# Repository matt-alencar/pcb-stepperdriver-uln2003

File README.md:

# Basic PCB based on ULN2003

Basic dual layer PCB project based on ULN2003 darlington transistor array, commonly used to drive unipolar stepper motor such as 28BYJ-48.

## Prerequisites

	Last version of KiCad software

## Versioning

	29/01/2019 - Initial work (V1.1)

## Authors

* **Matheus Alencar Nascimento** - *Initial work*

## License

This project is licensed under the MIT License - see the [LICENSE] file for details

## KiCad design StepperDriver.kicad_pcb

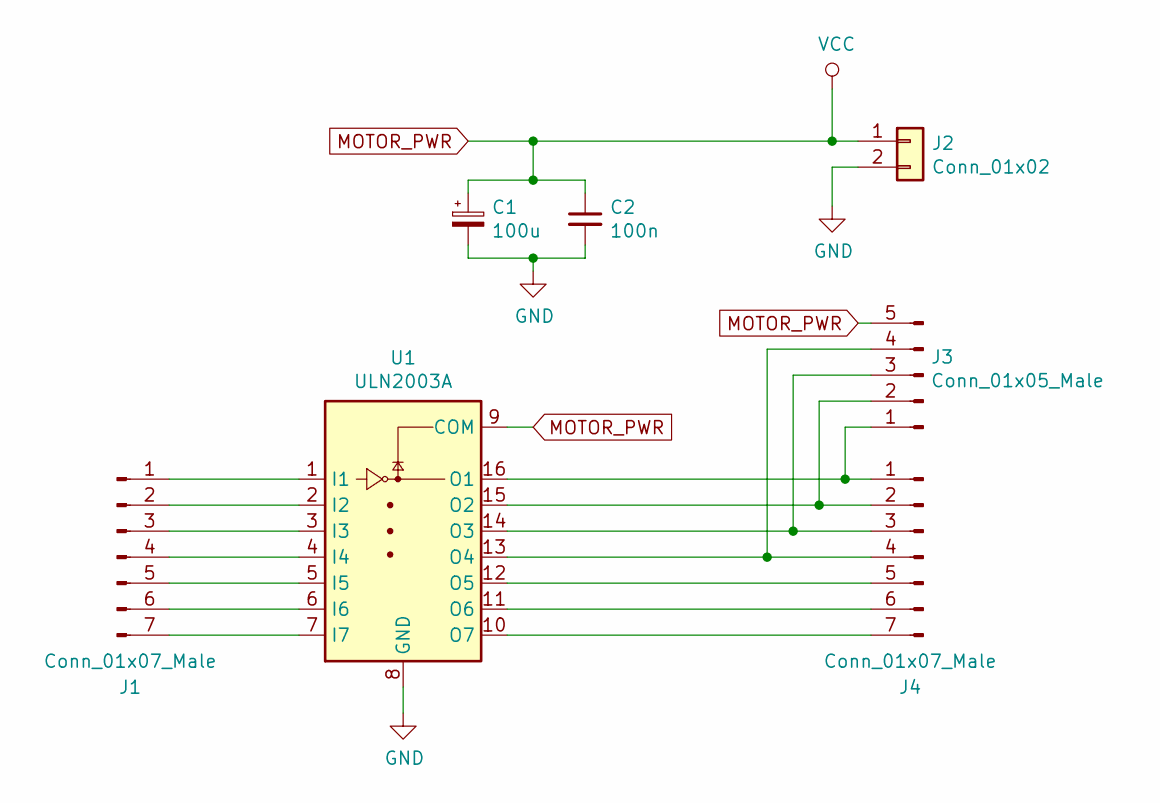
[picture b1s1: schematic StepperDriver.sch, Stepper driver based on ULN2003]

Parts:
C1: 100u; CP_Radial_D5.0mm_P2.00mm
C2: 100n; C_Rect_L4.6mm_W2.0mm_P2.50mm_MKS02_FKP02
J1, J4: Conn_01x07_Male; PinHeader_1x07_P2.54mm_Vertical
J2: Conn_01x02; TerminalBlock_RND_205-00232_1x02_P5.08mm_Horizontal
J3: Conn_01x05_Male; JST_XH_B05B-XH-A_1x05_P2.50mm_Vertical
U1: ULN2003A; DIP-16_W7.62mm

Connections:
GND: C1.2, C2.2, J2.2, U1.8 (GND)
MOTOR_PWR: C1.1, C2.1, J2.1, J3.5, U1.9 (COM)
unnamed: J1.1, U1.1 (I1)
unnamed: J1.2, U1.2 (I2)
unnamed: J1.3, U1.3 (I3)
unnamed: J1.4, U1.4 (I4)
unnamed: J1.5, U1.5 (I5)
unnamed: J1.6, U1.6 (I6)
unnamed: J1.7, U1.7 (I7)
unnamed: J3.1, J4.1, U1.16 (O1)
unnamed: J3.2, J4.2, U1.15 (O2)
unnamed: J3.3, J4.3, U1.14 (O3)
unnamed: J3.4, J4.4, U1.13 (O4)
unnamed: J4.5, U1.12 (O5)
unnamed: J4.6, U1.11 (O6)
unnamed: J4.7, U1.10 (O7)

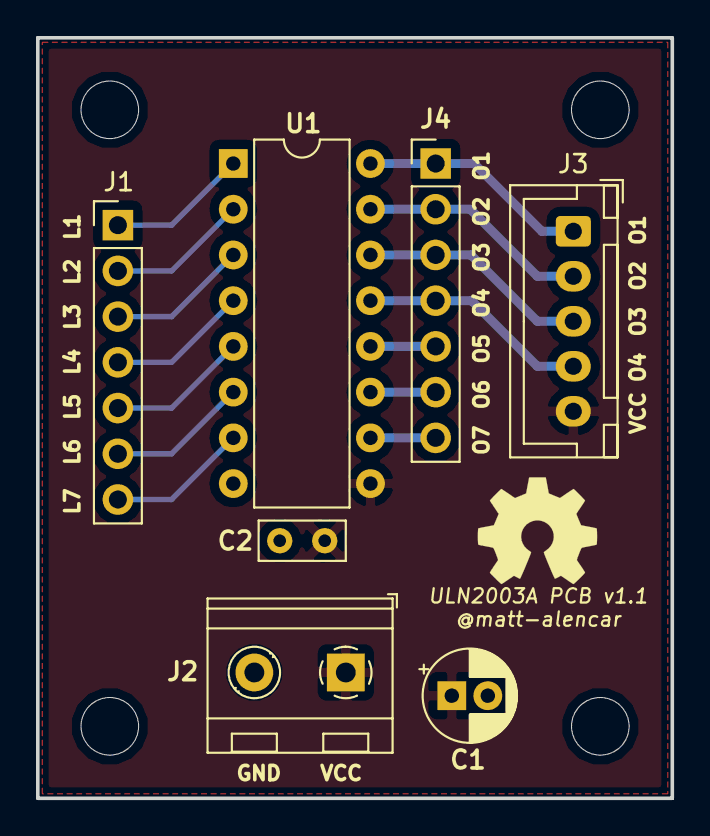
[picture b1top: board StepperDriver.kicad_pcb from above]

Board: 2 copper layers, 35.2 x 42.2 mm, 7 parts (0 on the bottom side), 16 nets.

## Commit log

2019-01-29 v1.1 up
